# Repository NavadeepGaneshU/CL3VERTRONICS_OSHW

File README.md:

# CL3VERTRONICS_OSHW
 CL3VERTRONICS - We are developing hardwares and availing PCB Schematic, Board layout, Design, Codes etc as Open-Source for everyone. Its solely for the benefit of Makers, Community and people out there!

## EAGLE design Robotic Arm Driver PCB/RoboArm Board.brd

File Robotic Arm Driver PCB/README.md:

This design includes 3 x DRV8884 stepper motor drivers and 1 x LMP91200 pH sensor integrated on a single PCB deployed for robotic farm sensing arm project.

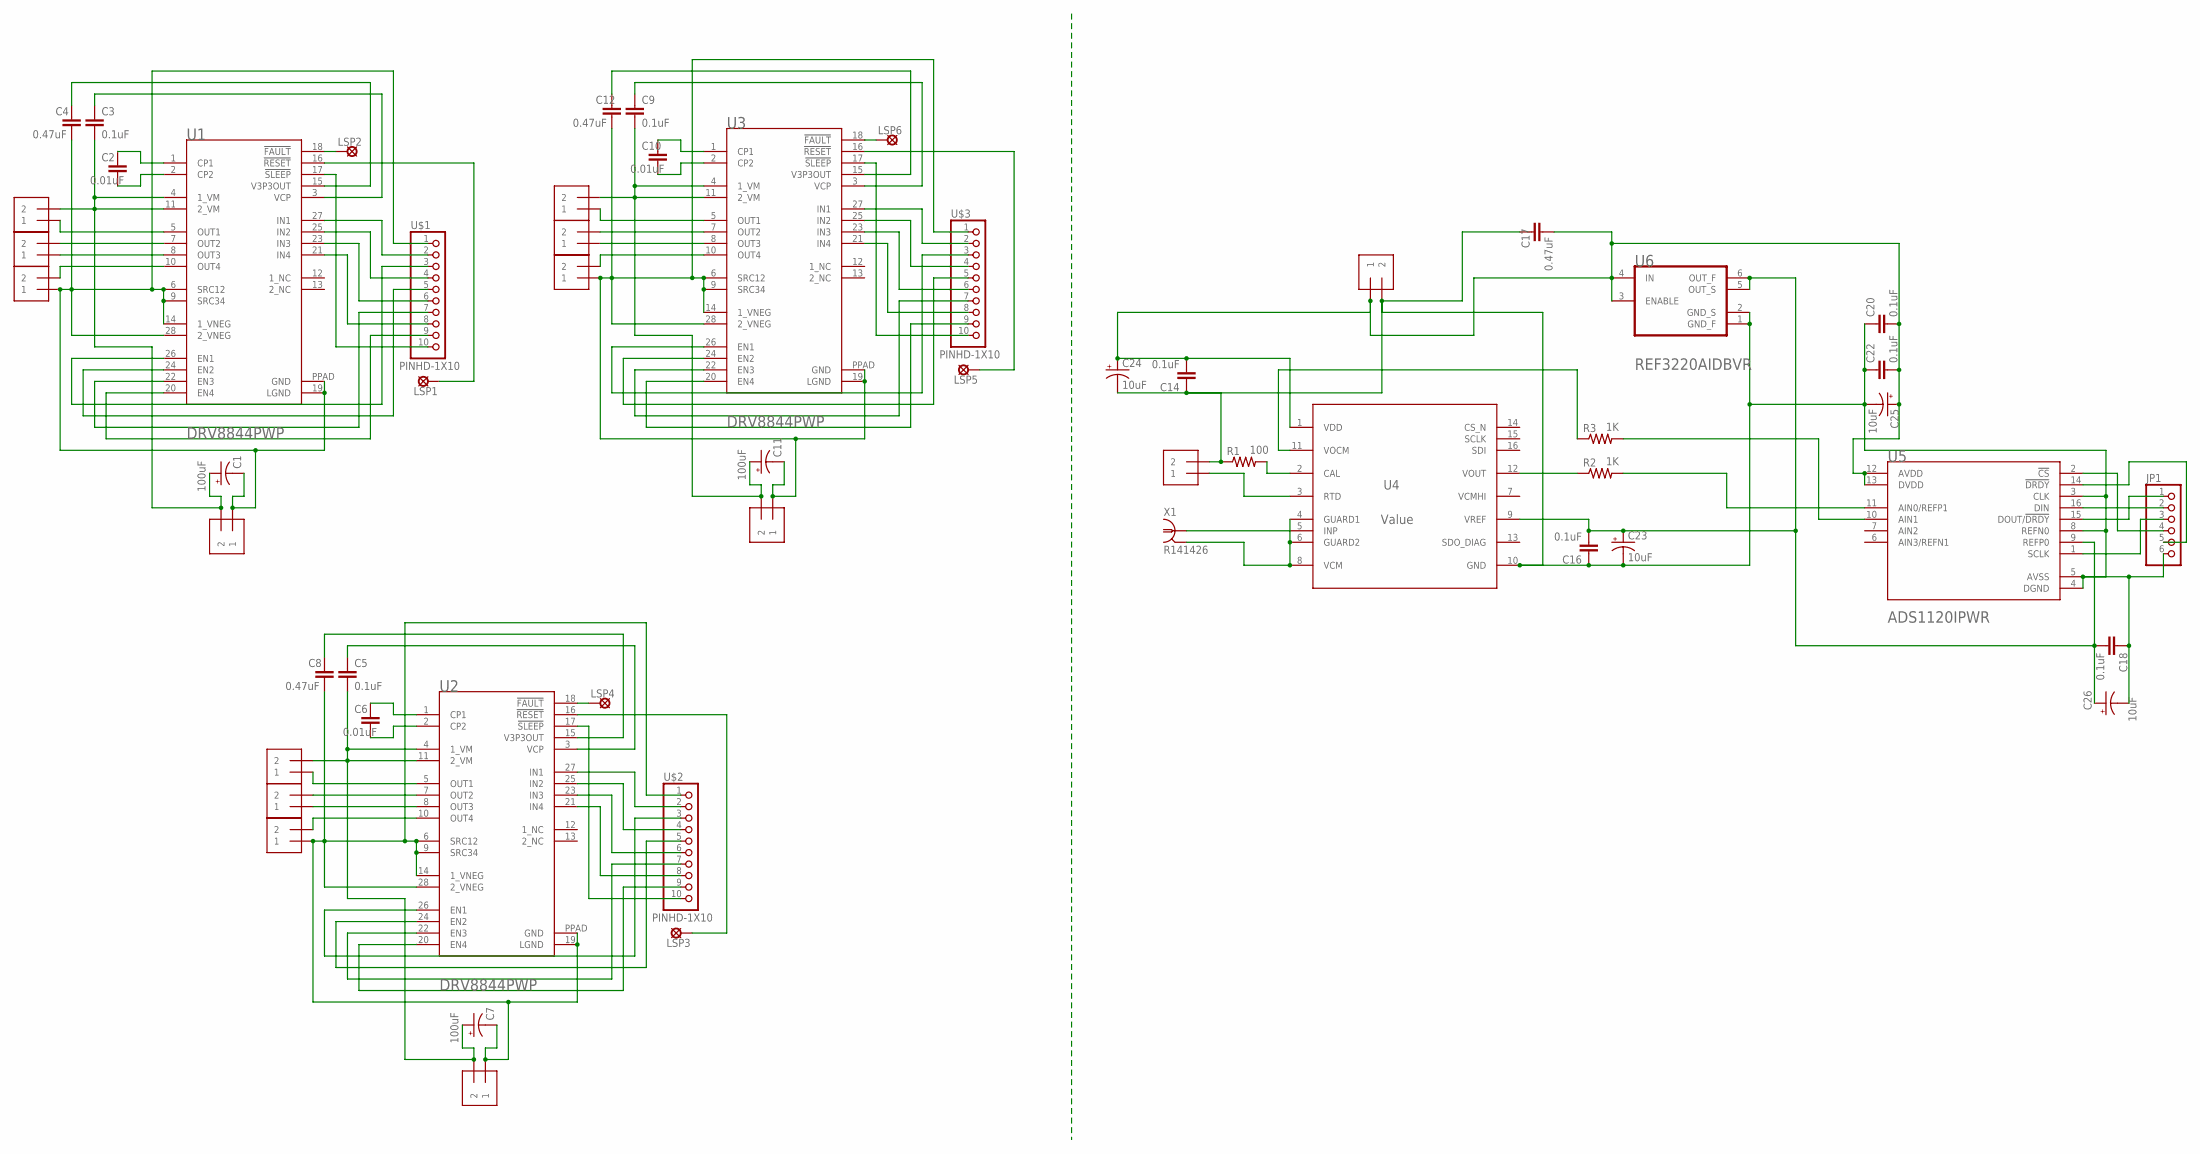
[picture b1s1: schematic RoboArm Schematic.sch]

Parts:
C1, C7, C11: 100uF; E5-8,5
C2, C6, C10: 0.01uF; C0805
C3, C5, C9, C14, C16, C18, C20, C22: 0.1uF; C0805
C4, C8, C12, C17: 0.47uF; C0805
C23, C24, C25, C26: 10uF; E2-4
J1, J2, J3, J4, J5, J6, J7, J8, J9, J10, J11, J12, J13, J15: 1X2-3.5MM
JP1: PINHD-1X6; 1X06
LSP1, LSP2, LSP3, LSP4, LSP5, LSP6: SE11
R1: 100; M0805
R2, R3: 1K; M0805
U1, U2, U3: TEXAS_INSTRUMENTS_DRV8844PWPTEXAS_INSTRUMENTS_DRV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; TEXAS_INSTRUMENTS_DRV8844PWP_0
U4: Value; PW0016A_L
U5: TEXAS_INSTRUMENTS_ADS1120IPWRTEXAS_INSTRUMENTS_AD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; TEXAS_INSTRUMENTS_ADS1120IPWR_0
U6: TEXAS_INSTRUMENTS_REF3220AIDBVRTEXAS_INSTRUMENTS_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; TEXAS_INSTRUMENTS_REF3220AIDBVR_1
U$1, U$2, U$3: PINHD-1X10; 1X10-BIG
X1: R141426

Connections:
unnamed: J2.1, U1.5 (OUT1)
unnamed: J3.2, U1.7 (OUT2)
unnamed: J3.1, U1.8 (OUT3)
unnamed: J4.2, U1.10 (OUT4)
unnamed: LSP2.MP, U1.18 (!FAULT!)
unnamed: J6.1, U2.5 (OUT1)
unnamed: C2.2, U1.2 (CP2)
unnamed: C2.1, U1.1 (CP1)
unnamed: C1.+, C3.2, J1.2, J2.2, U1.4 (1_VM), U1.11 (2_VM)
unnamed: C3.1, U1.3 (VCP)
unnamed: C4.1, U1.15 (V3P3OUT)
unnamed: C1.-, C4.2, J1.1, J4.1, U1.6 (SRC12), U1.9 (SRC34), U1.14 (1_VNEG), U1.19 (LGND), U1.28 (2_VNEG), U1.PPAD (GND), U$1.1
unnamed: J7.2, U2.7 (OUT2)
unnamed: U1.27 (IN1), U$1.2
unnamed: U1.25 (IN2), U$1.4
unnamed: U1.26 (EN1), U$1.3
unnamed: U1.24 (EN2), U$1.5
unnamed: U1.23 (IN3), U$1.6
unnamed: U1.22 (EN3), U$1.7
unnamed: U1.21 (IN4), U$1.8
unnamed: U1.20 (EN4), U$1.9
unnamed: U1.17 (!SLEEP!), U$1.10
unnamed: LSP1.MP, U1.16 (!RESET!)
unnamed: J7.1, U2.8 (OUT3)
unnamed: J8.2, U2.10 (OUT4)
unnamed: C6.2, U2.2 (CP2)
unnamed: C6.1, U2.1 (CP1)
unnamed: C5.2, C7.+, J5.2, J6.2, U2.4 (1_VM), U2.11 (2_VM)
unnamed: C5.1, U2.3 (VCP)
unnamed: U2.27 (IN1), U$2.2
unnamed: U2.25 (IN2), U$2.4
unnamed: U2.26 (EN1), U$2.3
unnamed: U2.24 (EN2), U$2.5
unnamed: U2.23 (IN3), U$2.6
unnamed: U2.22 (EN3), U$2.7
unnamed: U2.21 (IN4), U$2.8
unnamed: U2.20 (EN4), U$2.9
unnamed: U2.17 (!SLEEP!), U$2.10
unnamed: LSP3.MP, U2.16 (!RESET!)
unnamed: C8.1, U2.15 (V3P3OUT)
unnamed: LSP4.MP, U2.18 (!FAULT!)
unnamed: C7.-, C8.2, J5.1, J8.1, U2.6 (SRC12), U2.9 (SRC34), U2.14 (1_VNEG), U2.19 (LGND), U2.28 (2_VNEG), U2.PPAD (GND), U$2.1
unnamed: J10.1, U3.5 (OUT1)
unnamed: J11.2, U3.7 (OUT2)
unnamed: J11.1, U3.8 (OUT3)
unnamed: J12.2, U3.10 (OUT4)
unnamed: C10.2, U3.2 (CP2)
unnamed: C10.1, U3.1 (CP1)
unnamed: C9.2, C11.+, J9.2, J10.2, U3.4 (1_VM), U3.11 (2_VM)
unnamed: C9.1, U3.3 (VCP)
unnamed: U3.27 (IN1), U$3.2
unnamed: U3.25 (IN2), U$3.4
unnamed: U3.26 (EN1), U$3.3
unnamed: U3.24 (EN2), U$3.5
unnamed: U3.23 (IN3), U$3.6
unnamed: U3.22 (EN3), U$3.7
unnamed: U3.21 (IN4), U$3.8
unnamed: U3.20 (EN4), U$3.9
unnamed: U3.17 (!SLEEP!), U$3.10
unnamed: LSP5.MP, U3.16 (!RESET!)
unnamed: C12.1, U3.15 (V3P3OUT)
unnamed: LSP6.MP, U3.18 (!FAULT!)
unnamed: C11.-, C12.2, J9.1, J12.1, U3.6 (SRC12), U3.9 (SRC34), U3.14 (1_VNEG), U3.19 (LGND), U3.28 (2_VNEG), U3.PPAD (GND), U$3.1
unnamed: U4.5 (INP), X1.1
unnamed: R2.1, U4.12 (VOUT)
unnamed: U4.4 (GUARD1), U4.6 (GUARD2), U4.8 (VCM), X1.2, X1.3 (2), X1.4 (2), X1.5 (2)
unnamed: R1.2, U4.2 (CAL)
unnamed: J13.1, U4.3 (RTD)
unnamed: R3.1, U4.11 (VOCM)
unnamed: R2.2, U5.11 (AIN0/REFP1)
unnamed: R3.2, U5.10 (AIN1)
unnamed: C14.1, C16.1, C17.1, C18.1, C20.1, C22.1, C23.-, C24.-, C25.-, C26.-, J13.2, J15.2, JP1.6, R1.1, U4.10 (GND), U5.3 (CLK), U5.4 (DGND), U5.5 (AVSS), U5.8 (REFN0), U6.1 (GND_F), U6.2 (GND_S)
unnamed: JP1.1, U5.15 (DOUT/!DRDY!)
unnamed: C14.2, C17.2, C20.2, C22.2, C24.+, C25.+, J15.1, U4.1 (VDD), U5.12 (AVDD), U5.13 (DVDD), U6.3 (ENABLE), U6.4 (IN)
unnamed: JP1.2, U5.16 (DIN)
unnamed: JP1.3, U5.1 (SCLK)
unnamed: JP1.4, U5.2 (!CS!)
unnamed: JP1.5, U5.14 (!DRDY!)
unnamed: C16.2, C18.2, C23.+, C26.+, U4.9 (VREF), U5.9 (REFP0), U6.5 (OUT_S), U6.6 (OUT_F)

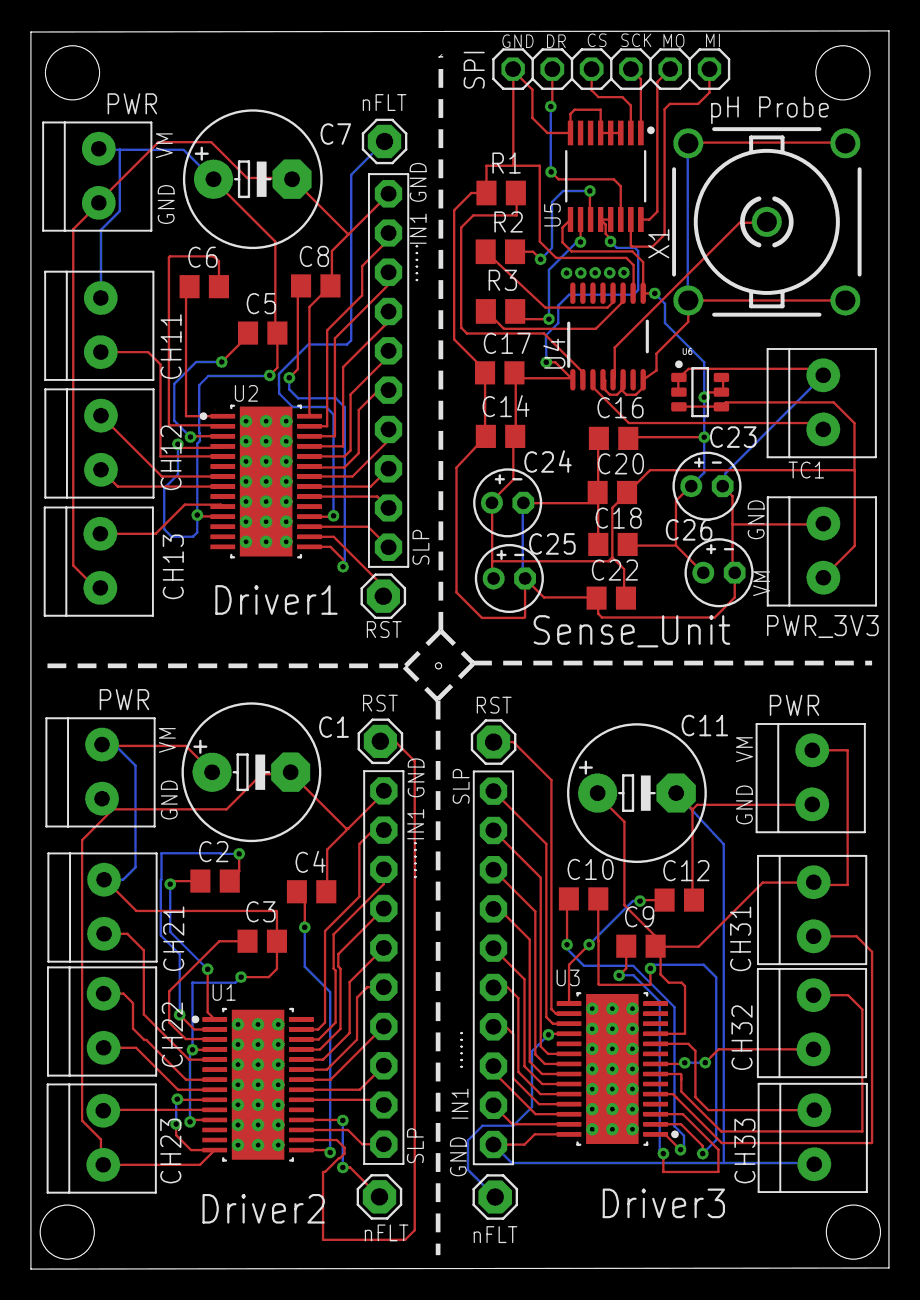
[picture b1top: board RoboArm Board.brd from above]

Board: 2 copper layers, 55.5 x 80.1 mm, 56 parts (0 on the bottom side), 79 nets.
